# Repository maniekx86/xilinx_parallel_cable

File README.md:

# xilinx_parallel_cable
Another clone of Xilinx parallel cable. The logic is based on what I had in my spare parts at the time of design (7404 + 7405).

## Usage
Connect this device to the PC using a DB-25 cable and provide +5V power to the J4 header, and you're ready to go.

## Pinout
### J4 (74xx logic power)
| Pin | Function  |
|-----|-----------|
| 1   | GND       |
| 2   | +5V       |

### J2 & J3 (connected together)
| Pin | Function  | Note                           |
|-----|-----------|--------------------------------|
| 1   | TMS       |                                |
| 2   | TCK       |                                |
| 3   | GND       |                                |
| 4   | TDO       |                                |
| 5   | TDI       |                                |
| 6   | Vref      | Connect to target device power |

## BOM
| Marking | Value/Element             | Package               | Amount |
|---------|---------------------------|-----------------------|--------|
| C1      | 100n                      | SMD 0805              | 1      |
| C2      | 10u                       | Radial D5.0mm P2.50mm | 1      |
| J1      | DB-25 female connector    |                       | 1      |
| J2      | Pin socket 1x6            | P2.54mm               | 1      |
| J3      | Pin header 1x6            | P2.54mm               | 1      |
| J4      | Pin header 1x2            | P2.54mm               | 1      |
| R1      | 100                       | SMD 0805              | 1      |
| R2-R4   | 470 (330 can be used too) | SMD 0805              | 3      |
| U1      | 7405                      | DIP-14                | 1      | 
| U2      | 7404                      | DIP-14                | 1      |

## Prototype
This design was tested on prototype PCB

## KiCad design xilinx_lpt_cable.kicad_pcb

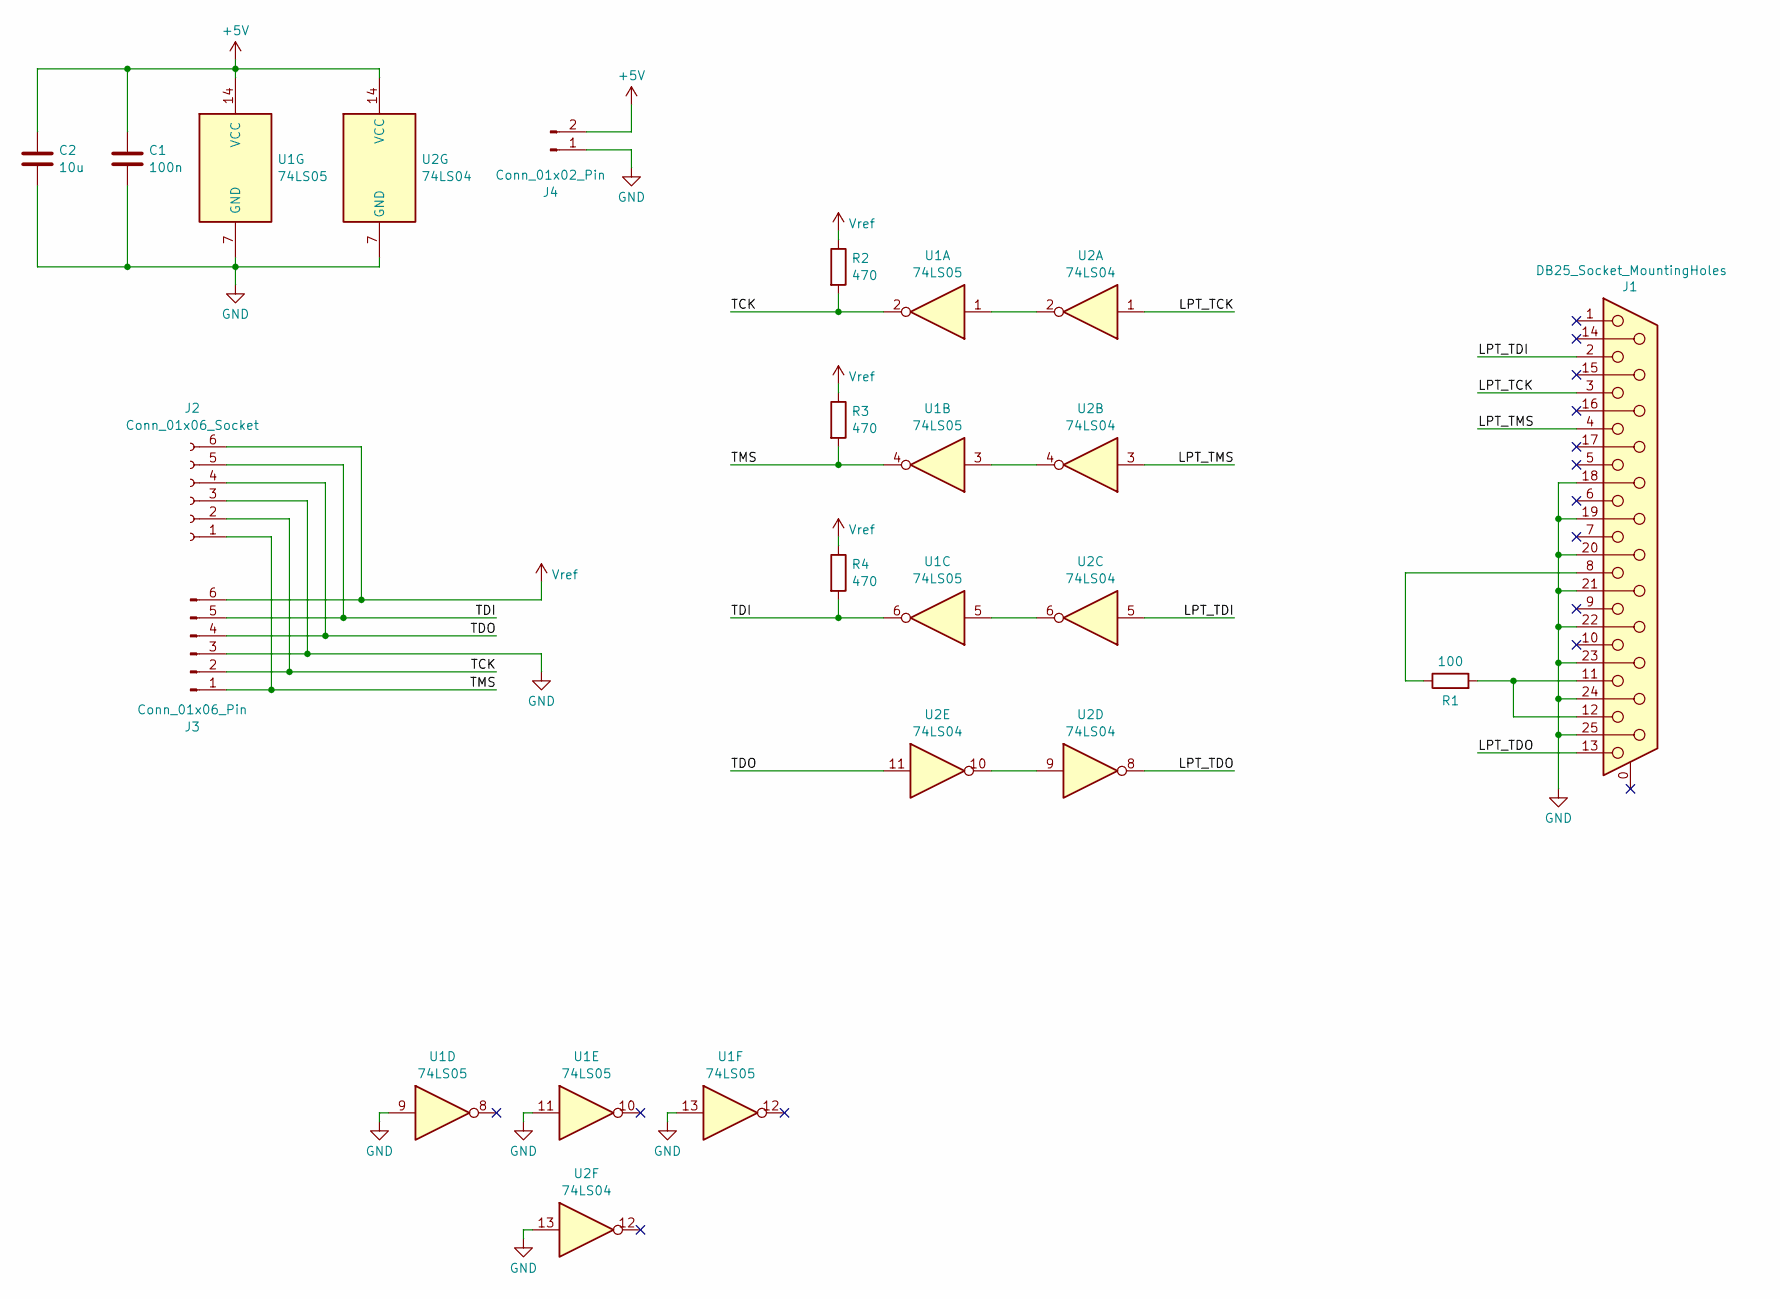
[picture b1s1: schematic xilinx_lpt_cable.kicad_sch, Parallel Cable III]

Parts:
C1: 100n; C_0805_2012Metric_Pad1.18x1.45mm_HandSolder
C2: 10u; CP_Radial_D5.0mm_P2.50mm
J1: DB25_Socket_MountingHoles; DSUB-25_Socket_Horizontal_P2.77x2.84mm_EdgePinOffset4.94mm_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
J2: Conn_01x06_Socket; PinSocket_1x06_P2.54mm_Vertical
J3: Conn_01x06_Pin; PinHeader_1x06_P2.54mm_Vertical
J4: Conn_01x02_Pin; PinHeader_1x02_P2.54mm_Vertical
R1: 100; R_0805_2012Metric_Pad1.20x1.40mm_HandSolder
R2, R3, R4: 470; R_0805_2012Metric_Pad1.20x1.40mm_HandSolder
U1: 74LS05; DIP-14_W7.62mm
U2: 74LS04; DIP-14_W7.62mm

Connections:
+5V: C1.1, C2.1, J4.2, U1.14 (VCC), U2.14 (VCC)
/LPT_TCK: J1.3, U2.1
/LPT_TDI: J1.2, U2.5
/LPT_TDO: J1.13, U2.8
/LPT_TMS: J1.4, U2.3
/TCK: J2.2, J3.2, R2.2, U1.2
/TDI: J2.5, J3.5, R4.2, U1.6
/TDO: J2.4, J3.4, U2.11
/TMS: J2.1, J3.1, R3.2, U1.4
GND: C1.2, C2.2, J1.18, J1.19, J1.20, J1.21, J1.22, J1.23, J1.24, J1.25, J2.3, J3.3, J4.1, U1.7 (GND), U1.9, U1.11, U1.13, U2.7 (GND), U2.13
unnamed: J1.8, R1.1
unnamed: J1.11, J1.12, R1.2
unnamed: U1.1, U2.2
unnamed: U1.3, U2.4
unnamed: U1.5, U2.6
unnamed: U2.9, U2.10
Vref: J2.6, J3.6, R2.1, R3.1, R4.1

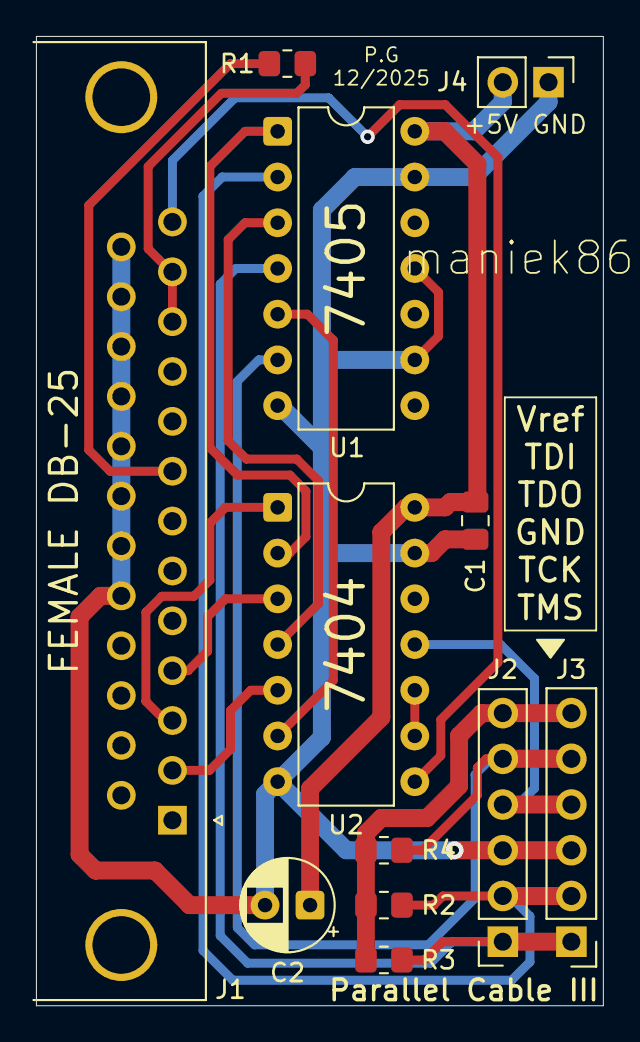
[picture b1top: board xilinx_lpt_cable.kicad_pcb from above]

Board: 2 copper layers, 31.5 x 53.8 mm, 12 parts (0 on the bottom side), 17 nets.

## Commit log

2025-12-14 Enhance README with usage, pinout, and BOM details
    Expanded the README with detailed usage instructions, pinout information, BOM, and prototype images.
2025-12-14 Compress prototype images
